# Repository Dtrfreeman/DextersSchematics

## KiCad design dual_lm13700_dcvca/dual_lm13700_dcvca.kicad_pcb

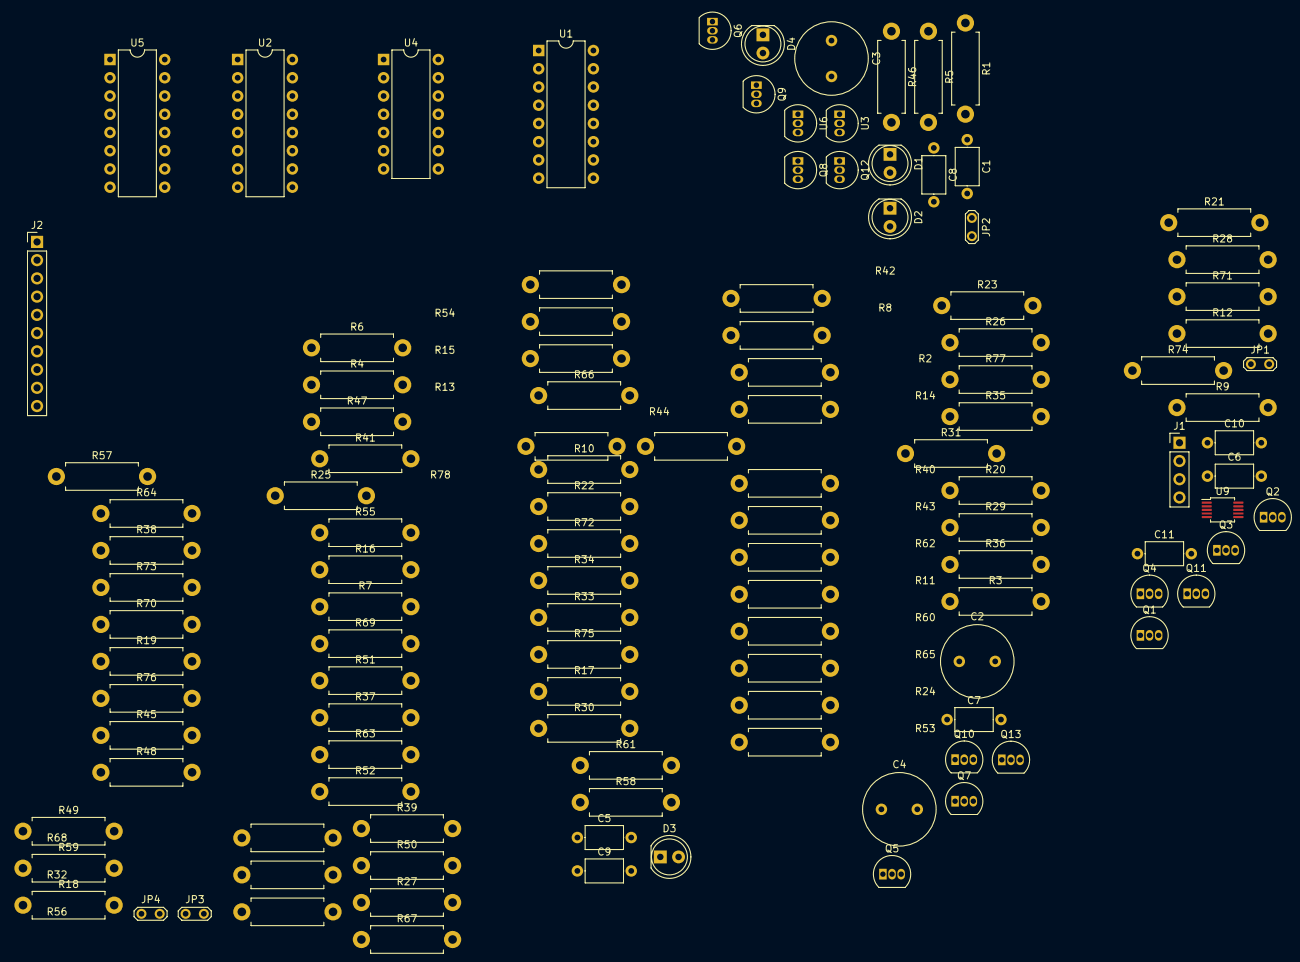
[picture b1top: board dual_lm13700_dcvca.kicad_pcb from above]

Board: 2 copper layers, 119 parts (0 on the bottom side), 94 nets, no tracks yet.

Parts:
C1, C5, C6, C7, C8, C9, C10, C11: C; C_Axial_L5.1mm_D3.1mm_P7.50mm_Horizontal
C2, C3, C4: C; C_Radial_D10.0mm_H12.5mm_P5.00mm
D1, D2, D3, D4: LED; LED_D5.0mm
J1: Conn_01x04_Male; PinHeader_1x04_P2.54mm_Vertical
J2: Conn_01x10_Male; PinHeader_1x10_P2.54mm_Vertical
JP1, JP3: Jumper_2_Bridged; TestPoint_2Pads_Pitch2.54mm_Drill0.8mm
JP2, JP4: Jumper_2_Open; TestPoint_2Pads_Pitch2.54mm_Drill0.8mm
Q1, Q3, Q5, Q7, Q9, Q11, Q13: 2N3904; TO-92_Inline
Q2, Q4, Q6, Q8, Q10, Q12: BF244C; TO-92_Inline
R1, R2, R3, R5, R6, R7, R8, R10, R16, R17, R22, R23, R24, R27, R28, R30, R31, R32, R33, R35, R36, R38, R39, R42, R43, R44, R45, R47, R53, R54, R59, R60, R61, R64, R65, R67, R68, R69, R70, R72, R73, R75, R77, R78: R; R_Axial_DIN0411_L9.9mm_D3.6mm_P12.70mm_Horizontal
R4, R9, R14, R15, R34, R40, R46, R51, R52, R71: 10k; R_Axial_DIN0411_L9.9mm_D3.6mm_P12.70mm_Horizontal
R11, R13, R18, R20, R21, R25, R29, R48, R50, R55, R57, R58, R62, R66: 100k; R_Axial_DIN0411_L9.9mm_D3.6mm_P12.70mm_Horizontal
R12, R26, R41, R49, R63, R76: 47k; R_Axial_DIN0411_L9.9mm_D3.6mm_P12.70mm_Horizontal
R19, R56: 20k; R_Axial_DIN0411_L9.9mm_D3.6mm_P12.70mm_Horizontal
R37, R74: 3k3; R_Axial_DIN0411_L9.9mm_D3.6mm_P12.70mm_Horizontal
U1, U2, U5: LM13700; DIP-16_W7.62mm
U3, U6: LM78L05_TO92; TO-92_Inline
U4: TL074; DIP-14_W7.62mm
U9: MCP4728; MSOP-10_3x3mm_P0.5mm

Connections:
+5V: C4.1, R2.1, R6.2, R7.2, R28.1, R32.2, R34.2, R35.1, R36.1, R43.2, R44.2, R65.1, R68.2, R71.2, R72.1, R73.1, U4.5 (+), U4.10 (+), U4.12 (+), U6.1 (VO), U9.1 (VDD)
+9V: C3.1, Q1.1 (E), R8.1, R13.2, R21.2, R29.2, R31.2, R45.1, R50.2, R58.2, R66.2, R69.2, U1.11 (V+), U2.11 (V+), U3.3 (VI), U4.4 (V+), U5.11 (V+), U6.3 (VI)
/BPa: J2.2, R18.1
/BPb: J2.5, R55.1
/DAC_Clock: J2.9, U9.2 (SCL)
/DAC_Data: J2.10, U9.3 (SDA)
/Digital5v: J2.8, U3.1 (VO)
/HPa: J2.1, R11.1
/HPb: J2.4, R48.1
/Input: C1.1, J1.3
/LPa: J2.3, R25.1
/LPb: J2.6, R62.1
/Output: C11.1, J1.4, R77.1
/Vin: J1.1, R1.2
GND: C2.2, C3.2, C4.2, C5.1, C6.1, C8.1, C10.1, J1.2, J2.7, Q3.1 (E), Q5.1 (E), Q7.1 (E), Q9.1 (E), Q11.1 (E), Q13.1 (E), R15.2, R20.2, R23.1, R39.1, R52.2, R57.2, R60.1, R77.2, R78.1, U1.6 (V-), U2.6 (V-), U3.2 (GND), U4.11 (V-), U5.6 (V-), U6.2 (GND), U9.10 (VSS)
unnamed: C2.1, Q1.2 (B), R3.1
unnamed: C8.2, U5.10, U5.12
unnamed: C10.2, U5.5, U5.7
unnamed: D1.2 (A), D2.1 (K), R30.2
unnamed: D3.1 (K), D4.2 (A), R57.1, U2.5, U2.7
unnamed: D3.2 (A), D4.1 (K), R67.2
unnamed: JP1.2 (B), JP2.1 (A), R33.2
unnamed: JP3.1 (A), R67.1, R72.2, U2.4 (-)
unnamed: JP3.2 (B), JP4.1 (A), R70.2
unnamed: JP4.2 (B), R73.2, U2.3 (+)
unnamed: Q1.3 (C), R1.1, R3.2
unnamed: Q2.1 (D), R4.1, R5.1, R9.2, R14.2
unnamed: Q2.2 (G), R10.1
unnamed: Q2.3 (S), R12.2
unnamed: Q3.2 (B), R11.2
unnamed: Q3.3 (C), R10.2, R13.1
unnamed: Q4.2 (G), R16.1
unnamed: Q4.3 (S), R19.2
unnamed: Q5.2 (B), R18.2
unnamed: Q5.3 (C), R16.2, R21.1
unnamed: Q6.1 (D), R34.1, R37.1
unnamed: Q6.2 (G), R24.1
unnamed: Q6.3 (S), R26.2
unnamed: Q7.2 (B), R25.2
unnamed: Q7.3 (C), R24.2, R29.1
unnamed: Q8.1 (D), R40.1, R42.1, R46.2, R51.2
unnamed: Q8.2 (G), R47.1
unnamed: Q8.3 (S), R49.2
unnamed: Q9.2 (B), R48.2
unnamed: Q9.3 (C), R47.2, R50.1
unnamed: Q10.1 (D), R60.2, R64.2, R70.1, U5.9
unnamed: Q10.2 (G), R53.1
unnamed: Q10.3 (S), R56.2
unnamed: Q11.2 (B), R55.2
unnamed: Q11.3 (C), R53.2, R58.1
unnamed: Q12.1 (D), R71.1, R74.1
unnamed: Q12.2 (G), R61.1
unnamed: Q12.3 (S), R63.2
unnamed: Q13.2 (B), R62.2
unnamed: Q13.3 (C), R61.2, R66.1
unnamed: R17.1, R38.1, U9.6 (VOUTA)
unnamed: R22.2, U9.7 (VOUTB)
unnamed: R40.2, R74.2, R78.2, U5.8
unnamed: R42.2, R43.1, U5.13 (-)
unnamed: R44.1, U5.14 (+)
unnamed: R45.2, U5.15 (DIODE_BIAS)
unnamed: R51.1, R52.1, U2.8
unnamed: R54.1, R75.1, U9.8 (VOUTC)
unnamed: R54.2, U5.16
unnamed: R59.1, U2.1
unnamed: R59.2, U9.9 (VOUTD)
unnamed: R64.1, R65.2, U5.4 (-)
unnamed: R68.1, U5.3 (+)
unnamed: R69.1, U5.2 (DIODE_BIAS)
unnamed: R75.2, U5.1
unnamed: R38.2, U1.1
unnamed: R31.1, U1.2 (DIODE_BIAS)
unnamed: R32.1, U1.3 (+)
unnamed: R27.1, R28.2, U1.4 (-)
unnamed: C6.2, U1.5, U1.7
unnamed: R4.2, R37.2, R39.2, U1.8
unnamed: Q4.1 (D), R23.2, R27.2, R33.1, U1.9
unnamed: C5.2, U1.10, U1.12
unnamed: R5.2, R6.1, U1.13 (-)
unnamed: R7.1, U1.14 (+)
unnamed: R8.2, U1.15 (DIODE_BIAS)
unnamed: R17.2, U1.16
unnamed: R14.1, R15.1, U2.9
unnamed: D1.1 (K), D2.2 (A), R20.1, U2.10, U2.12
unnamed: JP1.1 (A), R30.1, R35.2, U2.13 (-)
unnamed: JP2.2 (B), R36.2, U2.14 (+)
unnamed: R22.1, U2.16
unnamed: R9.1, U4.1, U4.2 (-)
unnamed: C1.2, R2.2, U4.3 (+)
unnamed: C7.2, R12.1, R19.1, R26.1, R41.2, U4.6 (-)
unnamed: C7.1, R41.1, R46.1, U4.7
unnamed: C9.1, C11.2, R76.1, U4.8
unnamed: C9.2, R49.1, R56.1, R63.1, R76.2, U4.9 (-)
unnamed: U4.13 (-), U4.14

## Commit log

2022-07-05 Schematics from 2018-2022
2022-12-20 Adding tarfile member sanitization to extractall()
